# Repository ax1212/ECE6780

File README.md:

# ECE6780
projects and assignments for ECE 6780, Embedded Systems.

By Alexander Mitchell, U1210600

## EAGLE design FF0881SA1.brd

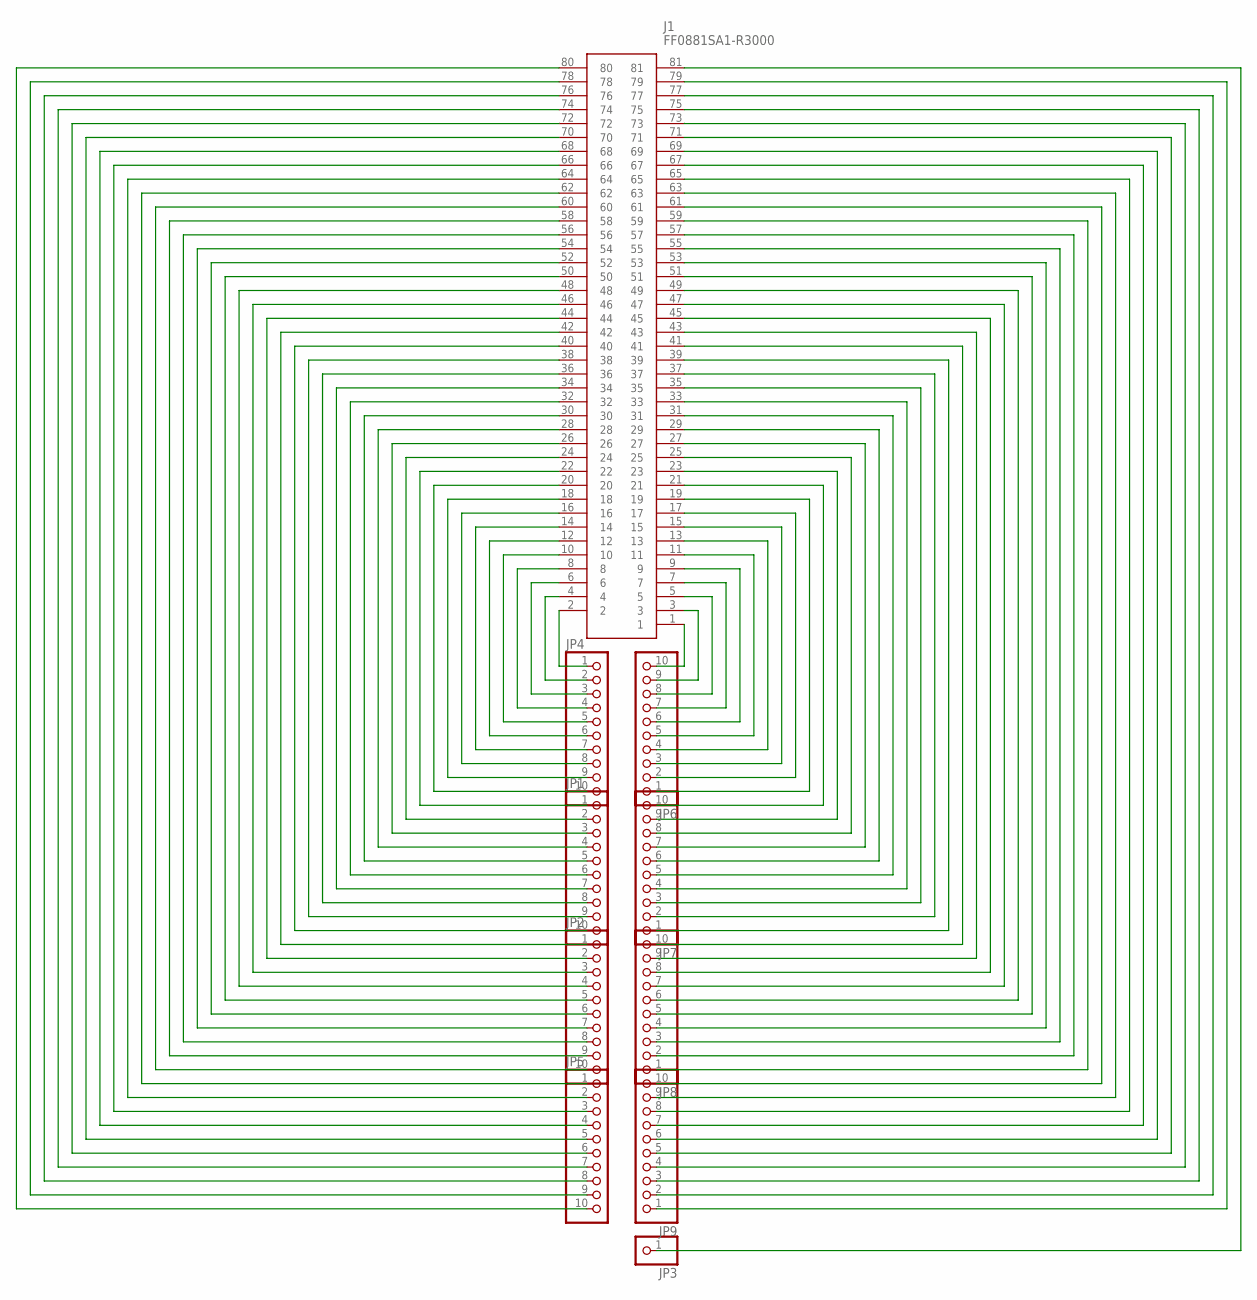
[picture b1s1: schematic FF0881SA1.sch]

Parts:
J1: FF0881SA1-R3000; FF0881SA1R3000
JP1, JP2, JP4, JP5, JP6, JP7, JP8, JP9: PINHD-1X10; 1X10
JP3: PINHD-1X1; 1X01

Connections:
unnamed: J1.1, JP6.10
unnamed: J1.3, JP6.9
unnamed: J1.5, JP6.8
unnamed: J1.7, JP6.7
unnamed: J1.9, JP6.6
unnamed: J1.11, JP6.5
unnamed: J1.13, JP6.4
unnamed: J1.15, JP6.3
unnamed: J1.17, JP6.2
unnamed: J1.19, JP6.1
unnamed: J1.21, JP7.10
unnamed: J1.23, JP7.9
unnamed: J1.2, JP4.1
unnamed: J1.4, JP4.2
unnamed: J1.6, JP4.3
unnamed: J1.8, JP4.4
unnamed: J1.10, JP4.5
unnamed: J1.12, JP4.6
unnamed: J1.14, JP4.7
unnamed: J1.16, JP4.8
unnamed: J1.18, JP4.9
unnamed: J1.20, JP4.10
unnamed: J1.22, JP1.1
unnamed: J1.24, JP1.2
unnamed: J1.26, JP1.3
unnamed: J1.28, JP1.4
unnamed: J1.30, JP1.5
unnamed: J1.32, JP1.6
unnamed: J1.34, JP1.7
unnamed: J1.36, JP1.8
unnamed: J1.38, JP1.9
unnamed: J1.40, JP1.10
unnamed: J1.42, JP2.1
unnamed: J1.44, JP2.2
unnamed: J1.25, JP7.8
unnamed: J1.27, JP7.7
unnamed: J1.29, JP7.6
unnamed: J1.31, JP7.5
unnamed: J1.33, JP7.4
unnamed: J1.35, JP7.3
unnamed: J1.37, JP7.2
unnamed: J1.39, JP7.1
unnamed: J1.41, JP8.10
unnamed: J1.43, JP8.9
unnamed: J1.46, JP2.3
unnamed: J1.48, JP2.4
unnamed: J1.50, JP2.5
unnamed: J1.52, JP2.6
unnamed: J1.54, JP2.7
unnamed: J1.56, JP2.8
unnamed: J1.58, JP2.9
unnamed: J1.60, JP2.10
unnamed: J1.62, JP5.1
unnamed: J1.64, JP5.2
unnamed: J1.66, JP5.3
unnamed: J1.68, JP5.4
unnamed: J1.70, JP5.5
unnamed: J1.72, JP5.6
unnamed: J1.74, JP5.7
unnamed: J1.76, JP5.8
unnamed: J1.78, JP5.9
unnamed: J1.80, JP5.10
unnamed: J1.45, JP8.8
unnamed: J1.47, JP8.7
unnamed: J1.49, JP8.6
unnamed: J1.51, JP8.5
unnamed: J1.53, JP8.4
unnamed: J1.55, JP8.3
unnamed: J1.57, JP8.2
unnamed: J1.59, JP8.1
unnamed: J1.61, JP9.10
unnamed: J1.63, JP9.9
unnamed: J1.65, JP9.8
unnamed: J1.67, JP9.7
unnamed: J1.69, JP9.6
unnamed: J1.71, JP9.5
unnamed: J1.73, JP9.4
unnamed: J1.75, JP9.3
unnamed: J1.77, JP9.2
unnamed: J1.79, JP9.1
unnamed: J1.81, JP3.1

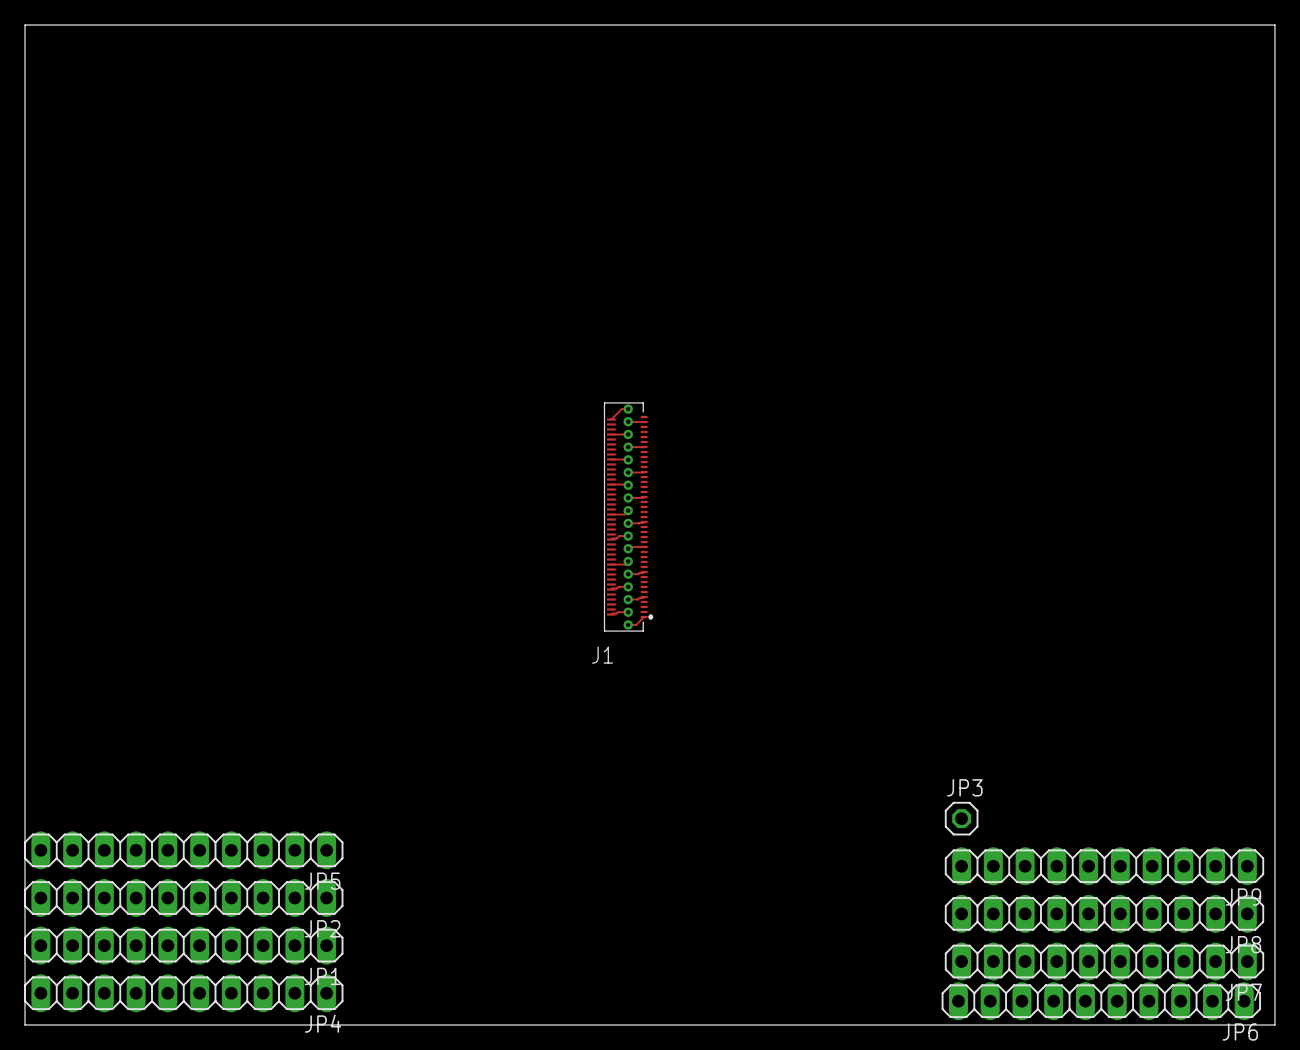
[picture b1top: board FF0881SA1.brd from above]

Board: 2 copper layers, 100.0 x 80.0 mm, 10 parts (0 on the bottom side), 81 nets.

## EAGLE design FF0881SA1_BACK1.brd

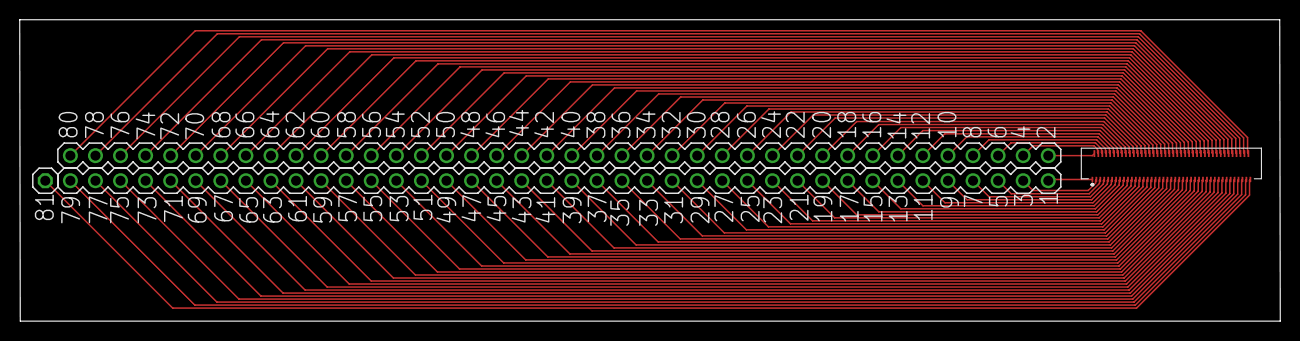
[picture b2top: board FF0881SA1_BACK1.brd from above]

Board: 2 copper layers, 127.7 x 30.5 mm, 4 parts (0 on the bottom side), 81 nets.

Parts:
J1: FF0881SA1-R3000; FF0881SA1R3000
JP1, JP2: 1X40
JP3: 1X01

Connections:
unnamed: J1.1, JP2.40
unnamed: J1.3, JP2.39
unnamed: J1.5, JP2.38
unnamed: J1.7, JP2.37
unnamed: J1.9, JP2.36
unnamed: J1.11, JP2.35
unnamed: J1.13, JP2.34
unnamed: J1.15, JP2.33
unnamed: J1.17, JP2.32
unnamed: J1.19, JP2.31
unnamed: J1.21, JP2.30
unnamed: J1.23, JP2.29
unnamed: J1.2, JP1.1
unnamed: J1.4, JP1.2
unnamed: J1.6, JP1.3
unnamed: J1.8, JP1.4
unnamed: J1.10, JP1.5
unnamed: J1.12, JP1.6
unnamed: J1.14, JP1.7
unnamed: J1.16, JP1.8
unnamed: J1.18, JP1.9
unnamed: J1.20, JP1.10
unnamed: J1.22, JP1.11
unnamed: J1.24, JP1.12
unnamed: J1.26, JP1.13
unnamed: J1.28, JP1.14
unnamed: J1.30, JP1.15
unnamed: J1.32, JP1.16
unnamed: J1.34, JP1.17
unnamed: J1.36, JP1.18
unnamed: J1.38, JP1.19
unnamed: J1.40, JP1.20
unnamed: J1.42, JP1.21
unnamed: J1.44, JP1.22
unnamed: J1.25, JP2.28
unnamed: J1.27, JP2.27
unnamed: J1.29, JP2.26
unnamed: J1.31, JP2.25
unnamed: J1.33, JP2.24
unnamed: J1.35, JP2.23
unnamed: J1.37, JP2.22
unnamed: J1.39, JP2.21
unnamed: J1.41, JP2.20
unnamed: J1.43, JP2.19
unnamed: J1.46, JP1.23
unnamed: J1.48, JP1.24
unnamed: J1.50, JP1.25
unnamed: J1.52, JP1.26
unnamed: J1.54, JP1.27
unnamed: J1.56, JP1.28
unnamed: J1.58, JP1.29
unnamed: J1.60, JP1.30
unnamed: J1.62, JP1.31
unnamed: J1.64, JP1.32
unnamed: J1.66, JP1.33
unnamed: J1.68, JP1.34
unnamed: J1.70, JP1.35
unnamed: J1.72, JP1.36
unnamed: J1.74, JP1.37
unnamed: J1.76, JP1.38
unnamed: J1.78, JP1.39
unnamed: J1.80, JP1.40
unnamed: J1.45, JP2.18
unnamed: J1.47, JP2.17
unnamed: J1.49, JP2.16
unnamed: J1.51, JP2.15
unnamed: J1.53, JP2.14
unnamed: J1.55, JP2.13
unnamed: J1.57, JP2.12
unnamed: J1.59, JP2.11
unnamed: J1.61, JP2.10
unnamed: J1.63, JP2.9
unnamed: J1.65, JP2.8
unnamed: J1.67, JP2.7
unnamed: J1.69, JP2.6
unnamed: J1.71, JP2.5
unnamed: J1.73, JP2.4
unnamed: J1.75, JP2.3
unnamed: J1.77, JP2.2
unnamed: J1.79, JP2.1
unnamed: J1.81, JP3.1

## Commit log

2022-03-26 Create ImageReadMain
